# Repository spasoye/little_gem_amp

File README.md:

# little_gem_amp

Battery powered portable guitar amplifier based on [little gem amplifier](http://www.runoffgroove.com/littlegem.html).

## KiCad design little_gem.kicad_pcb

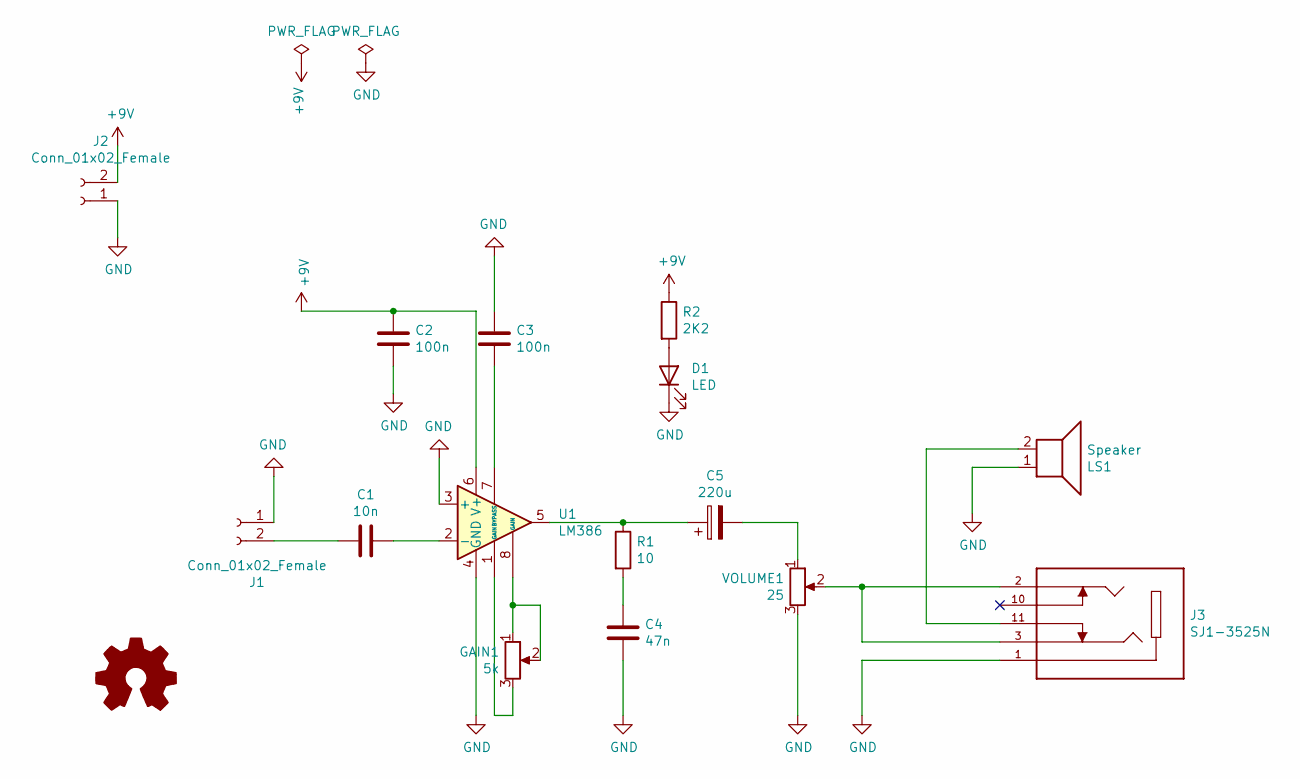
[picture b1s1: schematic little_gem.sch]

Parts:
C1: 10n; C_Rect_L7.2mm_W2.5mm_P5.00mm_FKS2_FKP2_MKS2_MKP2
C2, C3: 100n; C_Rect_L7.2mm_W2.5mm_P5.00mm_FKS2_FKP2_MKS2_MKP2
C4: 47n; C_Rect_L7.2mm_W2.5mm_P5.00mm_FKS2_FKP2_MKS2_MKP2
C5: 220u; CP_Radial_D6.3mm_P2.50mm
D1: LED; LED_D3.0mm
GAIN1: 5k; PinHeader_1x03_P2.54mm_Vertical
J1: Conn_01x02_Female; PinHeader_1x02_P2.54mm_Vertical
J2: Conn_01x02_Female; PinHeader_2x01_P2.54mm_Vertical
J3: SJ1-3525N; CUI_SJ1-3525N
LS1: Speaker; PinHeader_1x02_P2.54mm_Vertical
R1: 10; R_Axial_DIN0207_L6.3mm_D2.5mm_P10.16mm_Horizontal
R2: 2K2; R_Axial_DIN0207_L6.3mm_D2.5mm_P10.16mm_Horizontal
U1: LM386; DIP-8_W7.62mm_Socket_LongPads
VOLUME1: 25; PinHeader_1x03_P2.54mm_Vertical

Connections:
+9V: C2.1, J2.2, R2.1, U1.6 (V+)
GND: C2.2, C3.1, C4.2, D1.1 (K), J1.1, J2.1, J3.1, LS1.1, U1.3 (+), U1.4 (GND), VOLUME1.3
unnamed: C1.1, U1.2 (-)
unnamed: C1.2, J1.2
unnamed: C3.2, U1.7 (BYPASS)
unnamed: C4.1, R1.2
unnamed: C5.1, R1.1, U1.5
unnamed: C5.2, VOLUME1.1
unnamed: D1.2 (A), R2.2
unnamed: GAIN1.1, GAIN1.2, U1.8 (GAIN)
unnamed: GAIN1.3, U1.1 (GAIN)
unnamed: J3.2, J3.3, VOLUME1.2
unnamed: J3.11, LS1.2

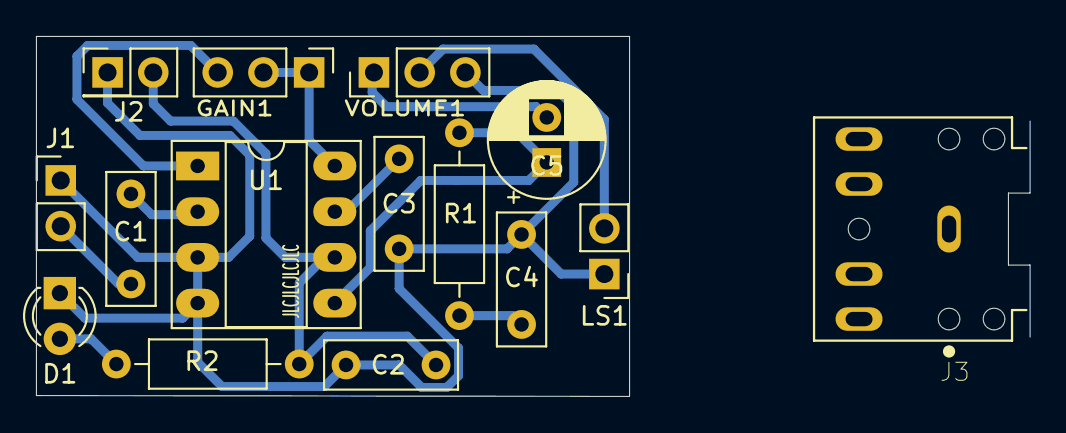
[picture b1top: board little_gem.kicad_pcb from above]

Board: 2 copper layers, 55.2 x 20.0 mm, 15 parts (0 on the bottom side), 13 nets.

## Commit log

2020-06-21 started with little gem amp
2020-06-24 Finished sch and pcb
2020-07-25 added .gitignore
2020-07-25 replaced footprints for pots and connectors
2020-07-25 added footprint for audio jack
2020-07-25 added mounting holes
2020-08-02 added PCB name
2020-08-02 added JLC order number location
2020-08-29 added power pins
2020-08-29 changed pot footprints
2020-09-02 Fixed footprints
2020-09-02 added led
2020-09-02 renamed
2020-09-02 one outside pic
2020-09-03 updated .gitignore
2020-09-03 added 3.5mm jack
